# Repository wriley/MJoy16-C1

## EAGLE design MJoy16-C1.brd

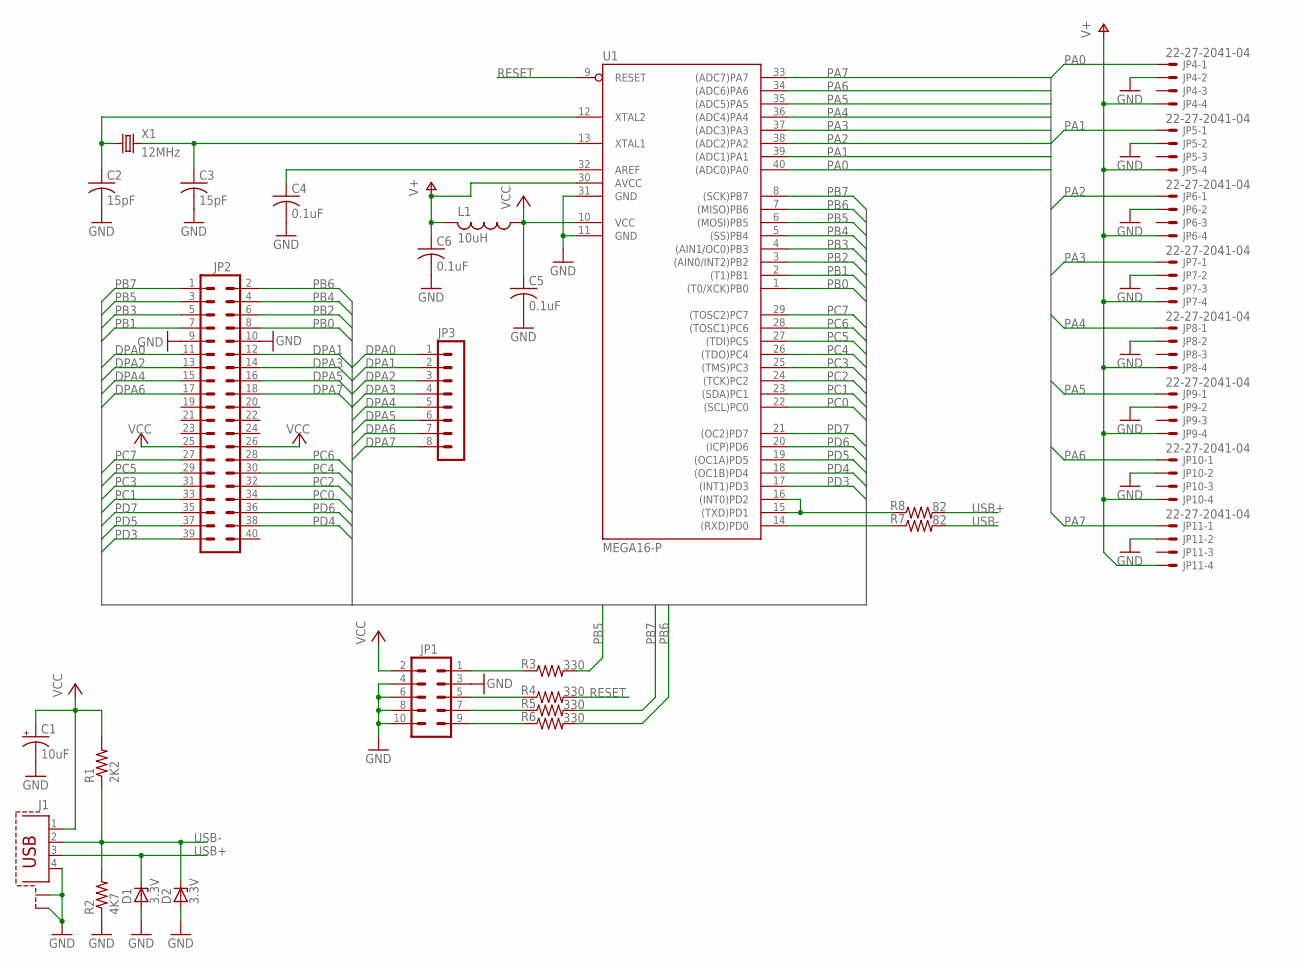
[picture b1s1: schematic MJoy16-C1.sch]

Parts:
C1: 10uF; E2,5-5
C2, C3: 15pF; C025-024X044
C4, C5, C6: 0.1uF; C050-025X075
D1, D2: 3.3V; ZDIO-5
J1: PN61729-S
JP1: ML10
JP2: MA20-2
JP3: MA08-1
JP4, JP5, JP6, JP7, JP8, JP9, JP10, JP11: 22-27-2041-04; 6410-04
L1: 10uH; 0207/7
R1: 2K2; 0207/7
R2: 4K7; 0207/7
R3, R4, R5, R6: 330; 0207/7
R7, R8: 82; 0207/7
U1: MEGA16-P; DIL40
X1: 12MHz; HC49U-V

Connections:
DPA0: JP2.11, JP3.1
DPA1: JP2.12, JP3.2
DPA2: JP2.13, JP3.3
DPA3: JP2.14, JP3.4
DPA4: JP2.15, JP3.5
DPA5: JP2.16, JP3.6
DPA6: JP2.17, JP3.7
DPA7: JP2.18, JP3.8
GND: C1.-, C2.2, C3.2, C4.2, C5.2, C6.2, D1.A, D2.A, J1.4, J1.S1, J1.S2, JP1.3, JP1.4, JP1.6, JP1.8, JP1.10, JP2.9, JP2.10, JP4.2, JP5.2, JP6.2, JP7.2, JP8.2, JP9.2, JP10.2, JP11.2, R2.1, U1.11 (GND), U1.31 (GND)
unnamed: JP1.1, R3.1
unnamed: JP1.5, R4.1
unnamed: JP1.7, R5.1
unnamed: JP1.9, R6.1
unnamed: C3.1, U1.13 (XTAL1), X1.2
unnamed: C2.1, U1.12 (XTAL2), X1.1
unnamed: C4.1, U1.32 (AREF)
unnamed: R7.1, U1.14 ((RXD)PD0)
unnamed: R8.1, U1.15 ((TXD)PD1), U1.16 ((INT0)PD2)
PA0: JP4.1, U1.40 ((ADC0)PA0)
PA1: JP5.1, U1.39 ((ADC1)PA1)
PA2: JP6.1, U1.38 ((ADC2)PA2)
PA3: JP7.1, U1.37 ((ADC3)PA3)
PA4: JP8.1, U1.36 ((ADC4)PA4)
PA5: JP9.1, U1.35 ((ADC5)PA5)
PA6: JP10.1, U1.34 ((ADC6)PA6)
PA7: JP11.1, U1.33 ((ADC7)PA7)
PB0: JP2.8, U1.1 ((T0/XCK)PB0)
PB1: JP2.7, U1.2 ((T1)PB1)
PB2: JP2.6, U1.3 ((AIN0/INT2)PB2)
PB3: JP2.5, U1.4 ((AIN1/OC0)PB3)
PB4: JP2.4, U1.5 ((SS)PB4)
PB5: JP2.3, R3.2, U1.6 ((MOSI)PB5)
PB6: JP2.2, R6.2, U1.7 ((MISO)PB6)
PB7: JP2.1, R5.2, U1.8 ((SCK)PB7)
PC0: JP2.34, U1.22 ((SCL)PC0)
PC1: JP2.33, U1.23 ((SDA)PC1)
PC2: JP2.32, U1.24 ((TCK)PC2)
PC3: JP2.31, U1.25 ((TMS)PC3)
PC4: JP2.30, U1.26 ((TDO)PC4)
PC5: JP2.29, U1.27 ((TDI)PC5)
PC6: JP2.28, U1.28 ((TOSC1)PC6)
PC7: JP2.27, U1.29 ((TOSC2)PC7)
PD3: JP2.39, U1.17 ((INT1)PD3)
PD4: JP2.38, U1.18 ((OC1B)PD4)
PD5: JP2.37, U1.19 ((OC1A)PD5)
PD6: JP2.36, U1.20 ((ICP)PD6)
PD7: JP2.35, U1.21 ((OC2)PD7)
RESET: R4.2, U1.9 (RESET)
USB+: D1.C, J1.3, R8.2
USB-: D2.C, J1.2, R1.1, R2.2, R7.2
V+: C6.1, JP4.4, JP5.4, JP6.4, JP7.4, JP8.4, JP9.4, JP10.4, JP11.4, L1.2, U1.30 (AVCC)
VCC: C1.+, C5.1, J1.1, JP1.2, JP2.25, JP2.26, L1.1, R1.2, U1.10 (VCC)

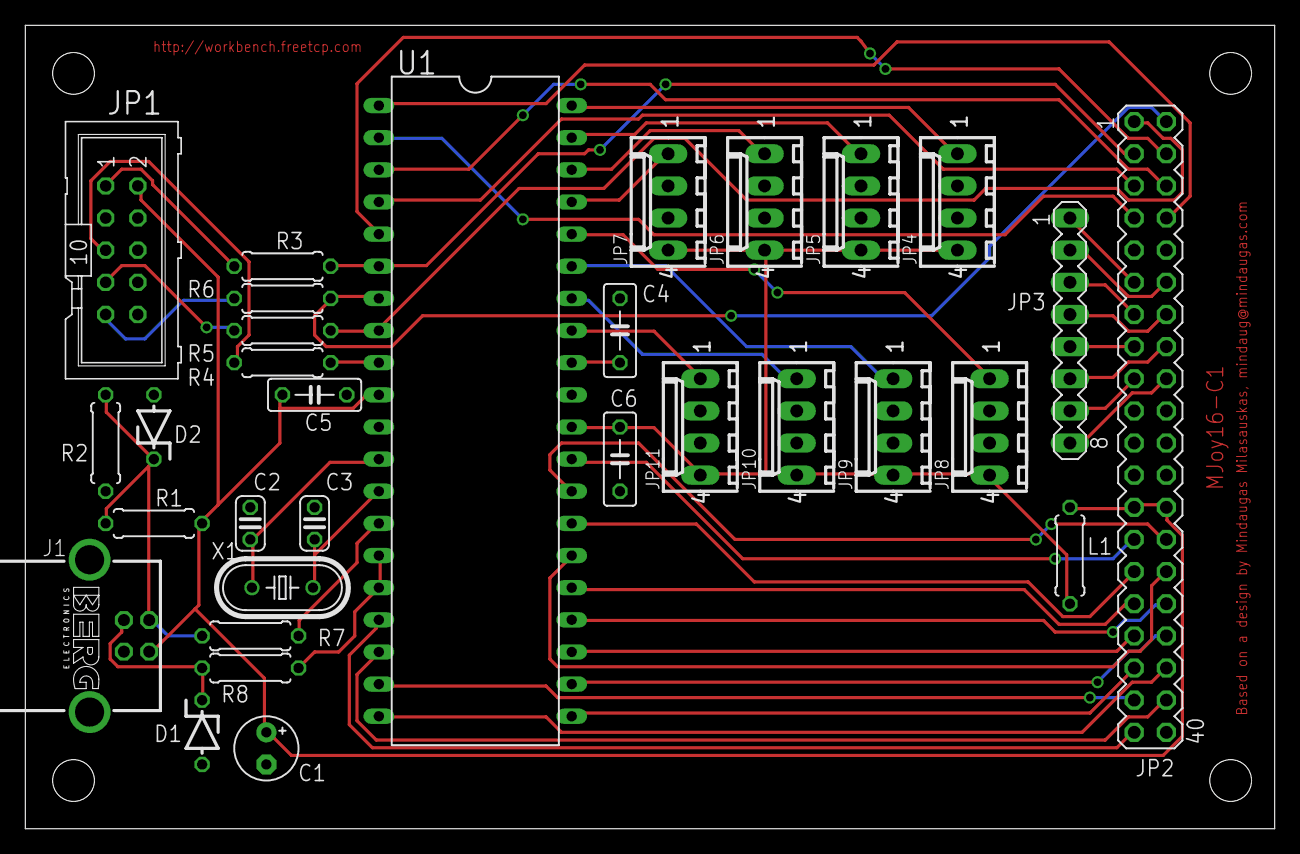
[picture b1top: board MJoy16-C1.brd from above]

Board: 2 copper layers, 98.7 x 63.5 mm, 35 parts (0 on the bottom side), 52 nets.

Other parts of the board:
U$1, U$2, U$3, U$4: STAND-OFF

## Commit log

2012-01-20 initial directory structure
2012-01-20 Added schematic
2012-01-20 Added board and Eagle3D files
2012-01-20 Added gerber output from LaenPCBOrder.cam
2012-01-21 tweaked ground plane polygon
2012-01-22 added text for original design by Mindaugas Milasauskas

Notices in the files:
parts and their libraries:
SparkFun: Licensing: CC v3.0 Share-Alike You are welcome to use this library for commercial purposes.
